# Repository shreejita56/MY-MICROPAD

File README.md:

# MY-MICROPAD

So I made a custom 2x4 Micropad based on Xiao RP2040 and it has  a rotor encoder on top . We have used diodes to prevent ghosting , the Switches are hot-swappable and it has a compact design.

<br>
The PCB Design was made on Kicad. Here I used the SMD Footprint for the Xiao Rp2040 and Hot-Swappable Footprint for the Switches . The rotor encoder at the top of the matrix also works as a switch . So In total We can use this MicroPad for 9 different Shortcuts and the rotor encoder can be used as a Volume Controller.Also It has per switch LEDS as well <br>

We have also used a Diode with each Switch , So that we can prevent Ghosting. The PCB also have few connection holes which helps it to connect with the CASE Properly.
<br>
I have tried to make the PCB design as compact as I could <br>

Lastly I made the Firmware for the PCB which I wrote completely in C language .

### Features
- 2x4 Switch Design with rotor encoder on top
- Per switch LED and Diode for ghosting
- Compact Design
- Two layered Case with base (Structured at an angle )

## Schematics 

## PCB 

## 3D Design 

# Bill of Materials (BOM)

| Item | Quantity | Price (USD) | Source |
|---|---:|---:|---|
| PCB + Shipping (after coupons) | 1 | $15.47 | [JLCPCB](https://jlcpcb.com/) |
| Seeed Studio XIAO RP2040 + Shipping | 1 | $5.10 | [Robocraze](https://robocraze.com/products/seeed-studio-xiao-rp2040-development-board?variant=47742255562976&country=IN&currency=INR) |
| Blank DSA Keycaps (pack of 5) | 2 packs (10 keycaps) | $1.05 | [Meckeys](https://meckeys.com/shop/accessories/keyboard-accessories/keycaps/blank/blank-dsa-keycaps-1u/?attribute_pa_variations=off-white) |
| HMX Snowfall Tactile Switches (pack of 10) | 1 pack (10 switches) | $3.57 | [NeoMacro](https://neomacro.in/products/hmx-snowfall-tactile-switch?variant=50878813503766) |
| Kailh Hot-Swap Sockets (pack of 10) | 1 pack (10 sockets) | $0.78 | [Meckeys](https://meckeys.com/shop/accessories/keyboard-accessories/key-switches/kailh-hot-swap-socket/) |
| Meckeys Shipping | 1 | $1.10 | [Meckeys](https://meckeys.com/) |
| Diodes | 10 pieces | $0.00 | Already owned |
| Rotary Encoder | 1 | $0.00 | Already owned |
|**TOTAL**||| **$27.07**|

**Total project cost: $27.07 USD**

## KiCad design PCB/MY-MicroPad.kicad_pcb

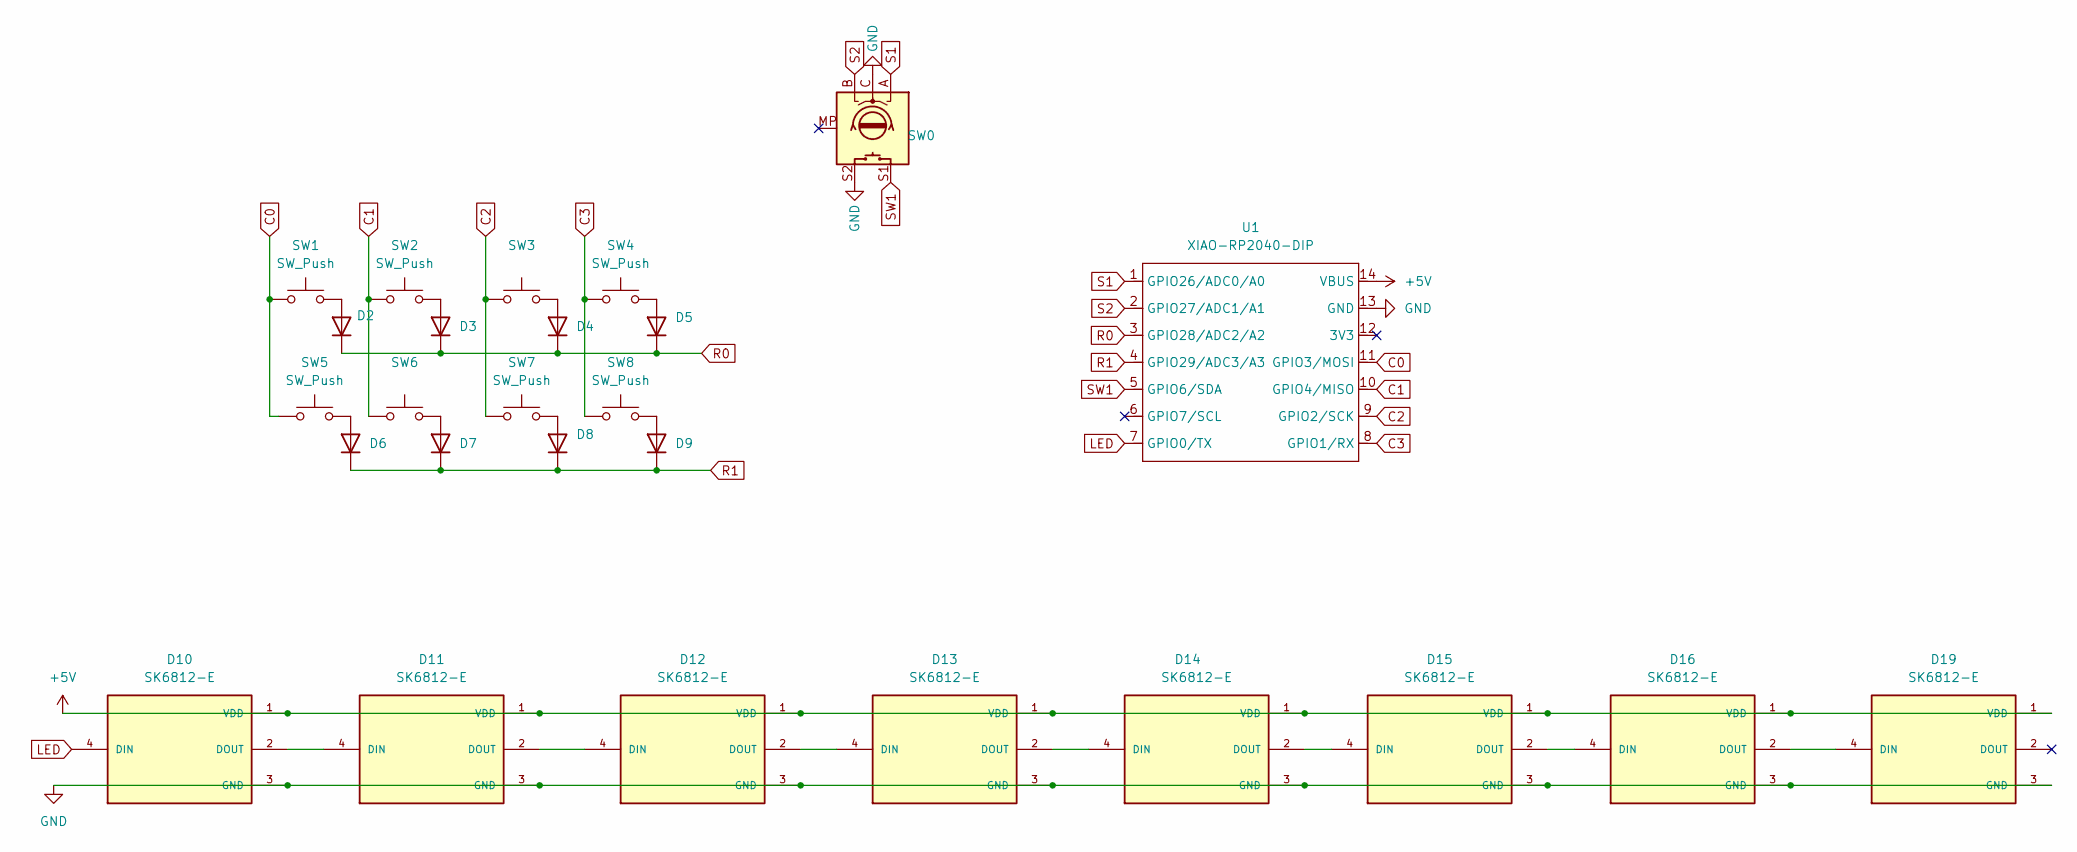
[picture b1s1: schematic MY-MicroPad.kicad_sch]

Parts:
D2, D3, D4, D5, D6, D7, D8, D9: 1N4148; D_DO-35_SOD27_P7.62mm_Horizontal
D10, D11, D12, D13, D14, D15, D16, D19: SK6812-E; LED_SK6812-E; PARTREV 2
SW0: RotaryEncoder_Switch_MP; RotaryEncoder_Alps_EC11E-Switch_Vertical_H20mm
SW1, SW2, SW3, SW4, SW5, SW6, SW7, SW8: SW_Push; MX100H
U1: XIAO-RP2040-DIP

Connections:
+5V: D10.1 (VDD), D11.1 (VDD), D12.1 (VDD), D13.1 (VDD), D14.1 (VDD), D15.1 (VDD), D16.1 (VDD), D19.1 (VDD), U1.14 (VBUS); also elsewhere on the board
C0: SW1.1, SW5.1, U1.11 (GPIO3/MOSI)
C1: SW2.1, SW6.1, U1.10 (GPIO4/MISO)
C2: SW3.1, SW7.1, U1.9 (GPIO2/SCK)
C3: SW4.1, SW8.1, U1.8 (GPIO1/RX)
GND: D10.3 (GND), D11.3 (GND), D12.3 (GND), D13.3 (GND), D14.3 (GND), D15.3 (GND), D16.3 (GND), D19.3 (GND), SW0.C, SW0.S2, U1.13 (GND); also elsewhere on the board
LED: D10.4 (DIN), U1.7 (GPIO0/TX)
unnamed: D2.2 (A), SW1.2
unnamed: D3.2 (A), SW2.2
unnamed: D4.2 (A), SW3.2
unnamed: D5.2 (A), SW4.2
unnamed: D6.2 (A), SW5.2
unnamed: D7.2 (A), SW6.2
unnamed: D8.2 (A), SW7.2
unnamed: D9.2 (A), SW8.2
unnamed: D10.2 (DOUT), D11.4 (DIN)
unnamed: D11.2 (DOUT), D12.4 (DIN)
unnamed: D12.2 (DOUT), D13.4 (DIN)
unnamed: D13.2 (DOUT), D14.4 (DIN)
unnamed: D14.2 (DOUT), D15.4 (DIN)
unnamed: D15.2 (DOUT), D16.4 (DIN)
unnamed 21: D16.2 (DOUT), D19.4 (DIN); also elsewhere on the board
R0: D2.1 (K), D3.1 (K), D4.1 (K), D5.1 (K), U1.3 (GPIO28/ADC2/A2)
R1: D6.1 (K), D7.1 (K), D8.1 (K), D9.1 (K), U1.4 (GPIO29/ADC3/A3)
S1: SW0.A, U1.1 (GPIO26/ADC0/A0)
S2: SW0.B, U1.2 (GPIO27/ADC1/A1)
SW1: SW0.S1, U1.5 (GPIO6/SDA)

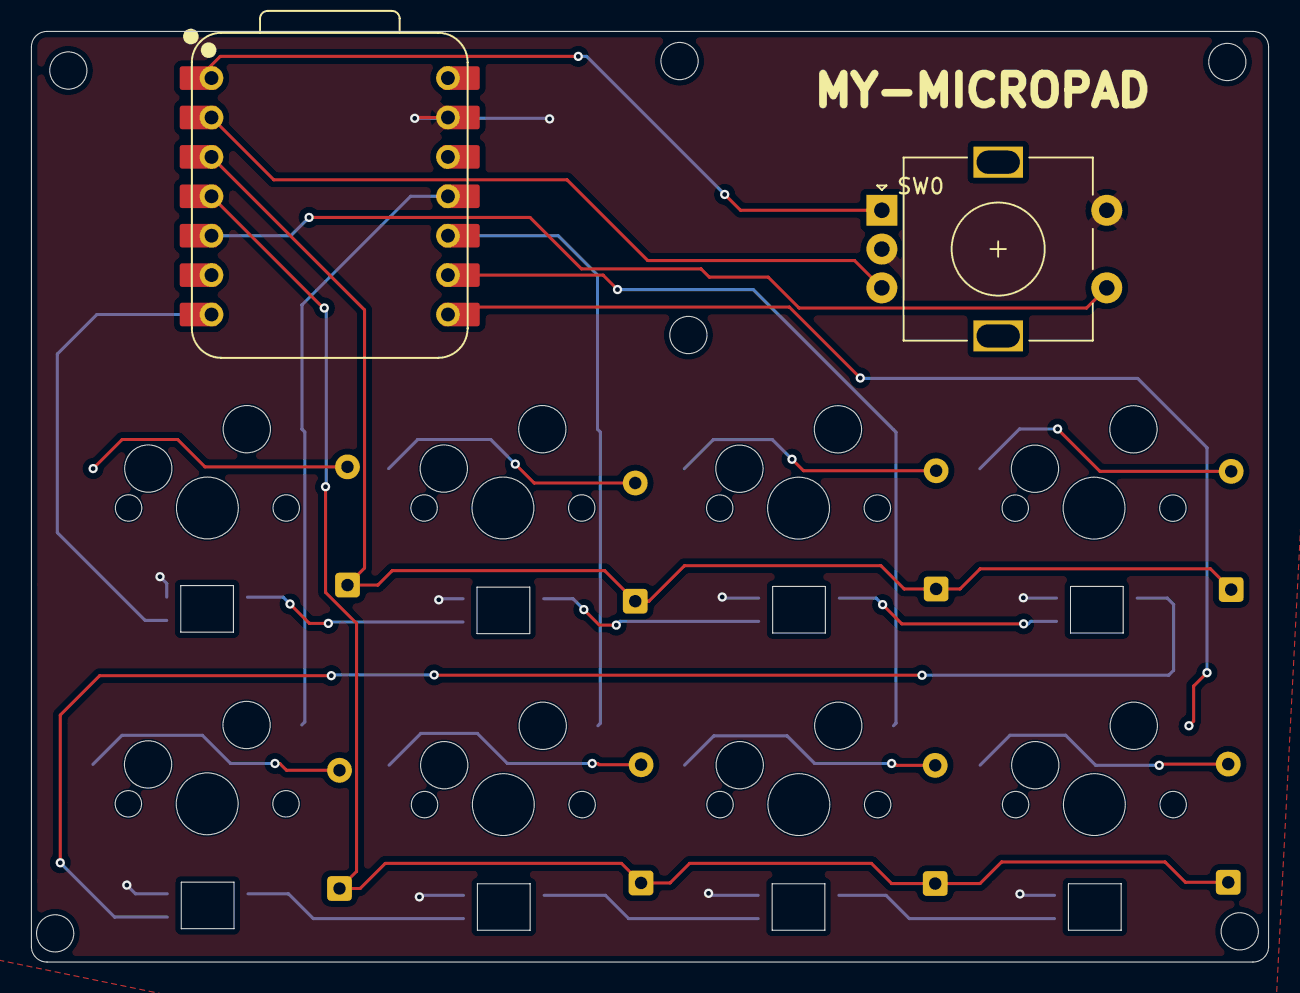
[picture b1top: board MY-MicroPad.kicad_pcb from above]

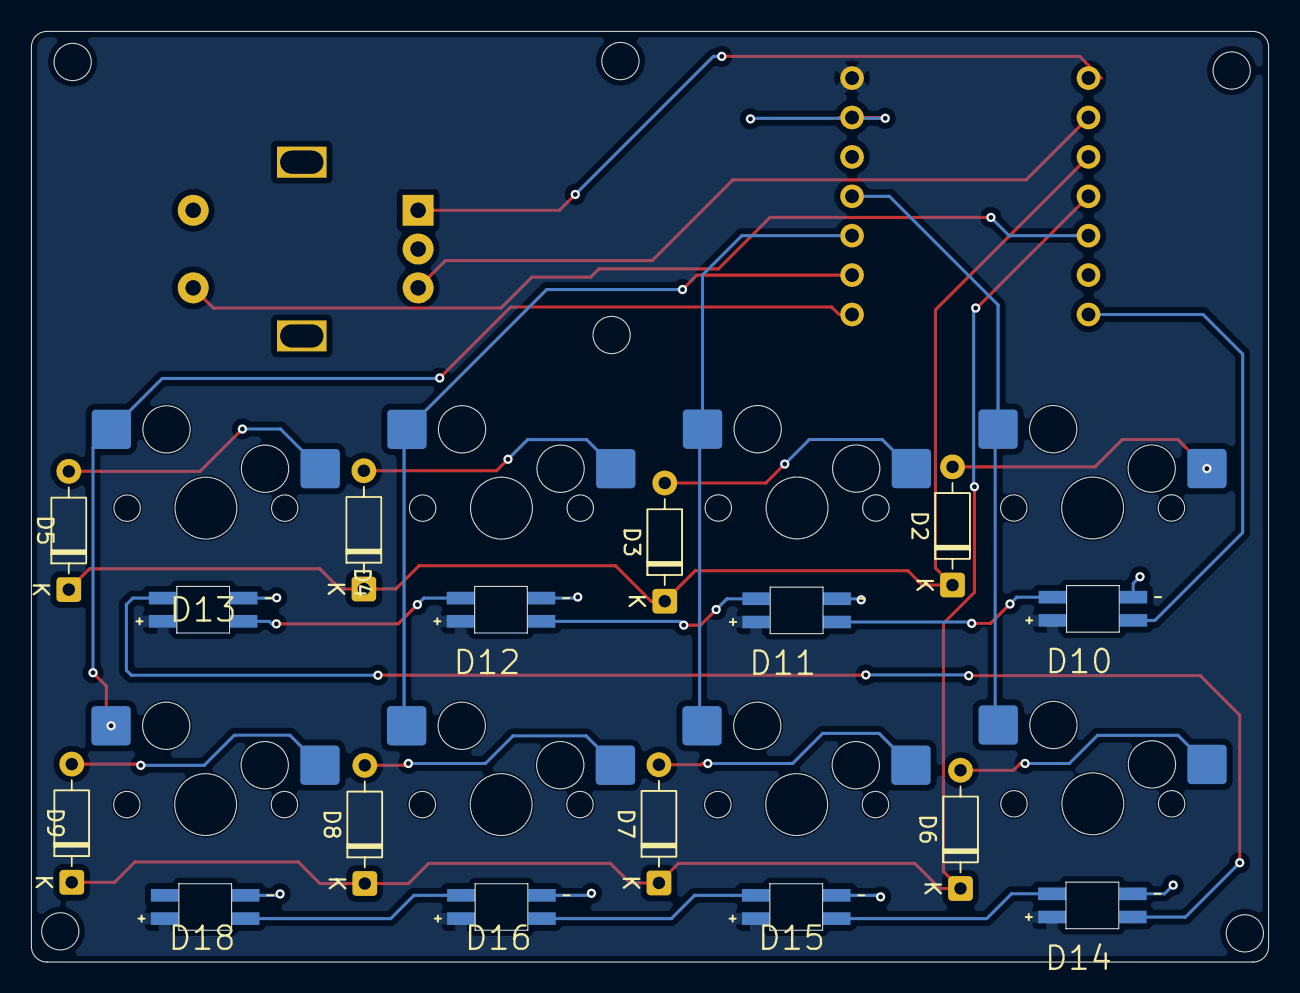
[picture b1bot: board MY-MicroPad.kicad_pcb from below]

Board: 2 copper layers, 79.8 x 60.0 mm, 26 parts (24 on the bottom side), 27 nets.

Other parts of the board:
D18: SK6812-E; LED_SK6812-E

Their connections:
+5V: D18.1 (VDD); also elsewhere on the board
GND: D18.3 (GND); also elsewhere on the board
unnamed 21: D18.4 (DIN); also elsewhere on the board
